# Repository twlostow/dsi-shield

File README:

DSI Core Readme
------------------------

0. Disclaimer

This project implements a MIPI DSI (MIPI Display Serial Interface) Verilog core.
Since the DSI specification is non-public and requires an NDA, the core was built
using bits and pieces available throughout the Web: presentations, display controller/SOC
datasheets, various application notes and Android kernel drivers. The author is not 
associated in any way with the MIPI Alliance. The core is provided as-is, it has never been
verified for compliance with the DSI standard and it probably lacks many of its features.
You use it at your own risk, there's no warranty.

1. License

- All HDL (unless otherwise noted) is released under LGPL v3.0
- All software (unless otherwise noted), is GPL v 3.0 or later.
- PCB design and schematics are licensed under CERN Open Hardware License v 1.2.

2. Acknowledgements

- Special thanks go to Sebastien Bourdeauducq, the creator of the Milkymist project, for his 
  excellent IP cores (HPDMC, FML and LM32 Xilinx port) used by in the DSI shield firmware.

- Andrew "Bunnie" Huang, for his EDID generation tools (Chumby WebTV project).

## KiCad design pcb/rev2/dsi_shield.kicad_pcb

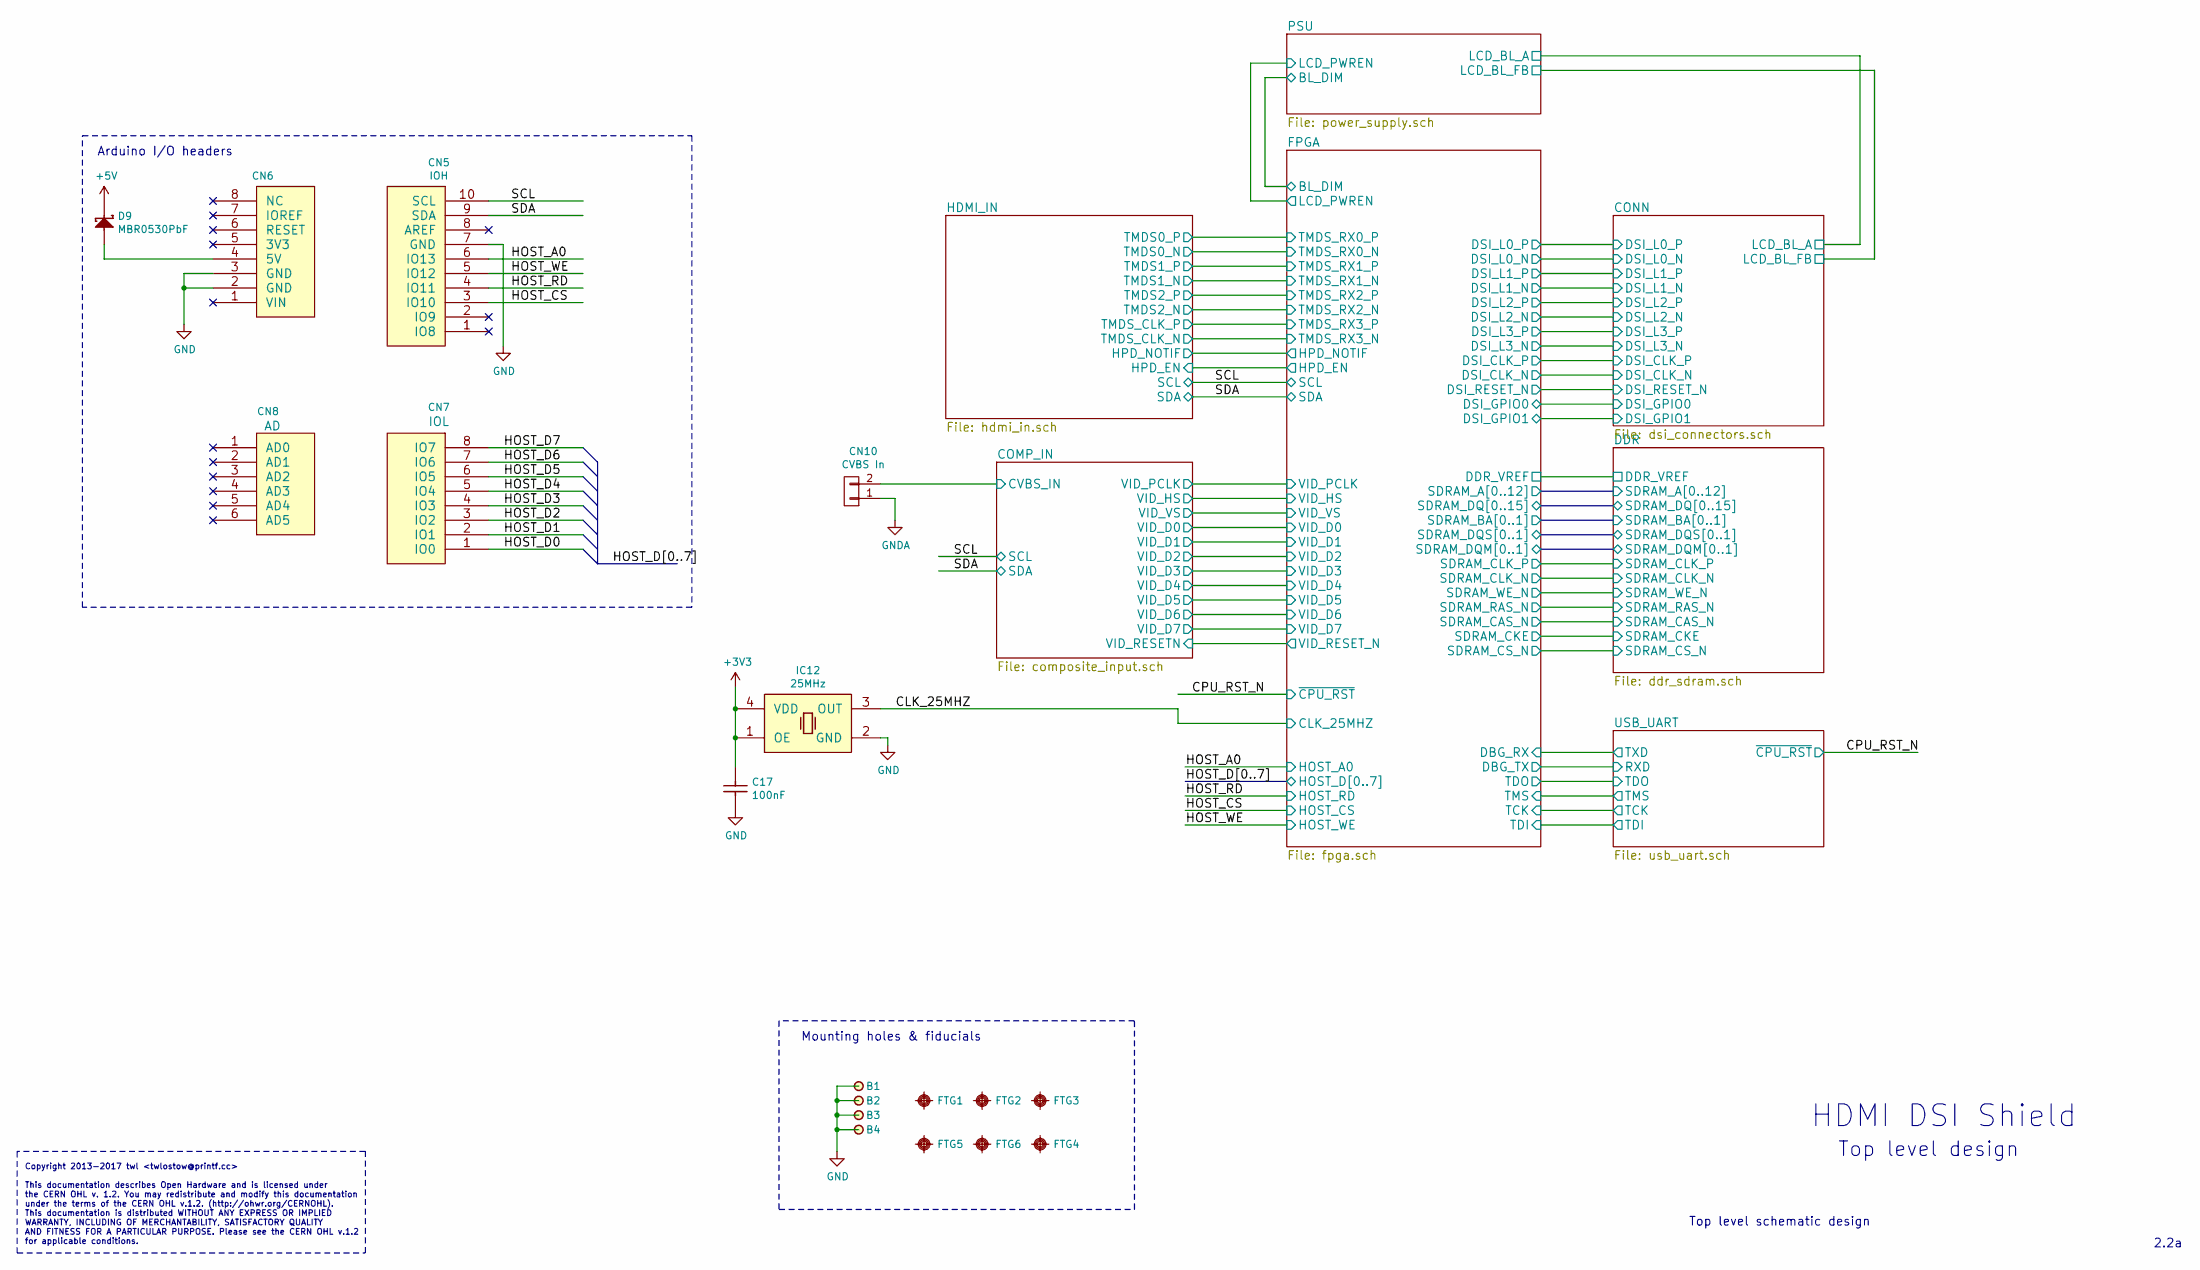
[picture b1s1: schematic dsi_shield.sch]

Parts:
B1, B2, B3, B4: PLATED_HOLE2.0_PAD3.5; c350h200; Part Number PLATED_HOLE2.0_PAD3.5
C17: CC0603_100NF_100V_10%_X7R; CAPC1608X90N; Voltage 100V; Tolerance ±10%; Part Number CC0603_100NF_100V_10%_X7R
CN5: IOH; Pin_Header_Straight_1x10
CN6: POWER_UNO; Pin_Header_Straight_1x08
CN7: IOL; Pin_Header_Straight_1x08
CN8: AD; Pin_Header_Straight_1x06
CN10: CVBS In; Pin_Header_Straight_1x02
D9: MBR0530PbF; SOD3715X145N; Voltage 30V; Part Number MBR0530PbF
FTG1, FTG2, FTG3, FTG4, FTG5, FTG6: FIDUCIAL_TARGET_S100-200; FIDUCIAL_TOP_S100-200; Part Number FIDUCIAL_TARGET_S100-200
IC12: OSC_25MHZ_PERICOM_FNETHE025; OSC_PERICOM_FNETHE025; Part Number OSC_25MHZ_PERICOM_FNETHE025

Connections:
+5V: D9.1 (C); also elsewhere on the board
/CLK_25MHZ: IC12.3 (OUT); also elsewhere on the board
/COMP_IN/CVBS_IN: CN10.2; also elsewhere on the board
/HOST_A0: CN5.6 (IO13); also elsewhere on the board
/HOST_CS: CN5.3 (IO10); also elsewhere on the board
/HOST_D0: CN7.1 (IO0); also elsewhere on the board
/HOST_D1: CN7.2 (IO1); also elsewhere on the board
/HOST_D2: CN7.3 (IO2); also elsewhere on the board
/HOST_D3: CN7.4 (IO3); also elsewhere on the board
/HOST_D4: CN7.5 (IO4); also elsewhere on the board
/HOST_D5: CN7.6 (IO5); also elsewhere on the board
/HOST_D6: CN7.7 (IO6); also elsewhere on the board
/HOST_D7: CN7.8 (IO7); also elsewhere on the board
/HOST_RD: CN5.4 (IO11); also elsewhere on the board
/HOST_WE: CN5.5 (IO12); also elsewhere on the board
/SCL: CN5.10 (SCL); also elsewhere on the board
/SDA: CN5.9 (SDA); also elsewhere on the board
GND: B1.1, B2.1, B3.1, B4.1, C17.2, CN5.7 (GND), CN6.2 (GND), CN6.3 (GND), IC12.2 (GND); also elsewhere on the board
GNDA: CN10.1; also elsewhere on the board
unnamed: CN6.4 (5V), D9.2 (A)

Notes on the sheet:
Copyright 2013-2017 twl <twlostow@printf.cc> This documentation describes Open Hardware and is licensed under the CERN OHL v. 1.2. You may redistribute and modify this documentation under the terms of the CERN OHL v.1.2. (http://ohwr.org/CERNOHL). This documentation is distributed WITHOUT ANY EXPRE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
HDMI DSI Shield
Top level design
2.2a
Top level schematic design
Mounting holes & fiducials
Arduino I/O headers

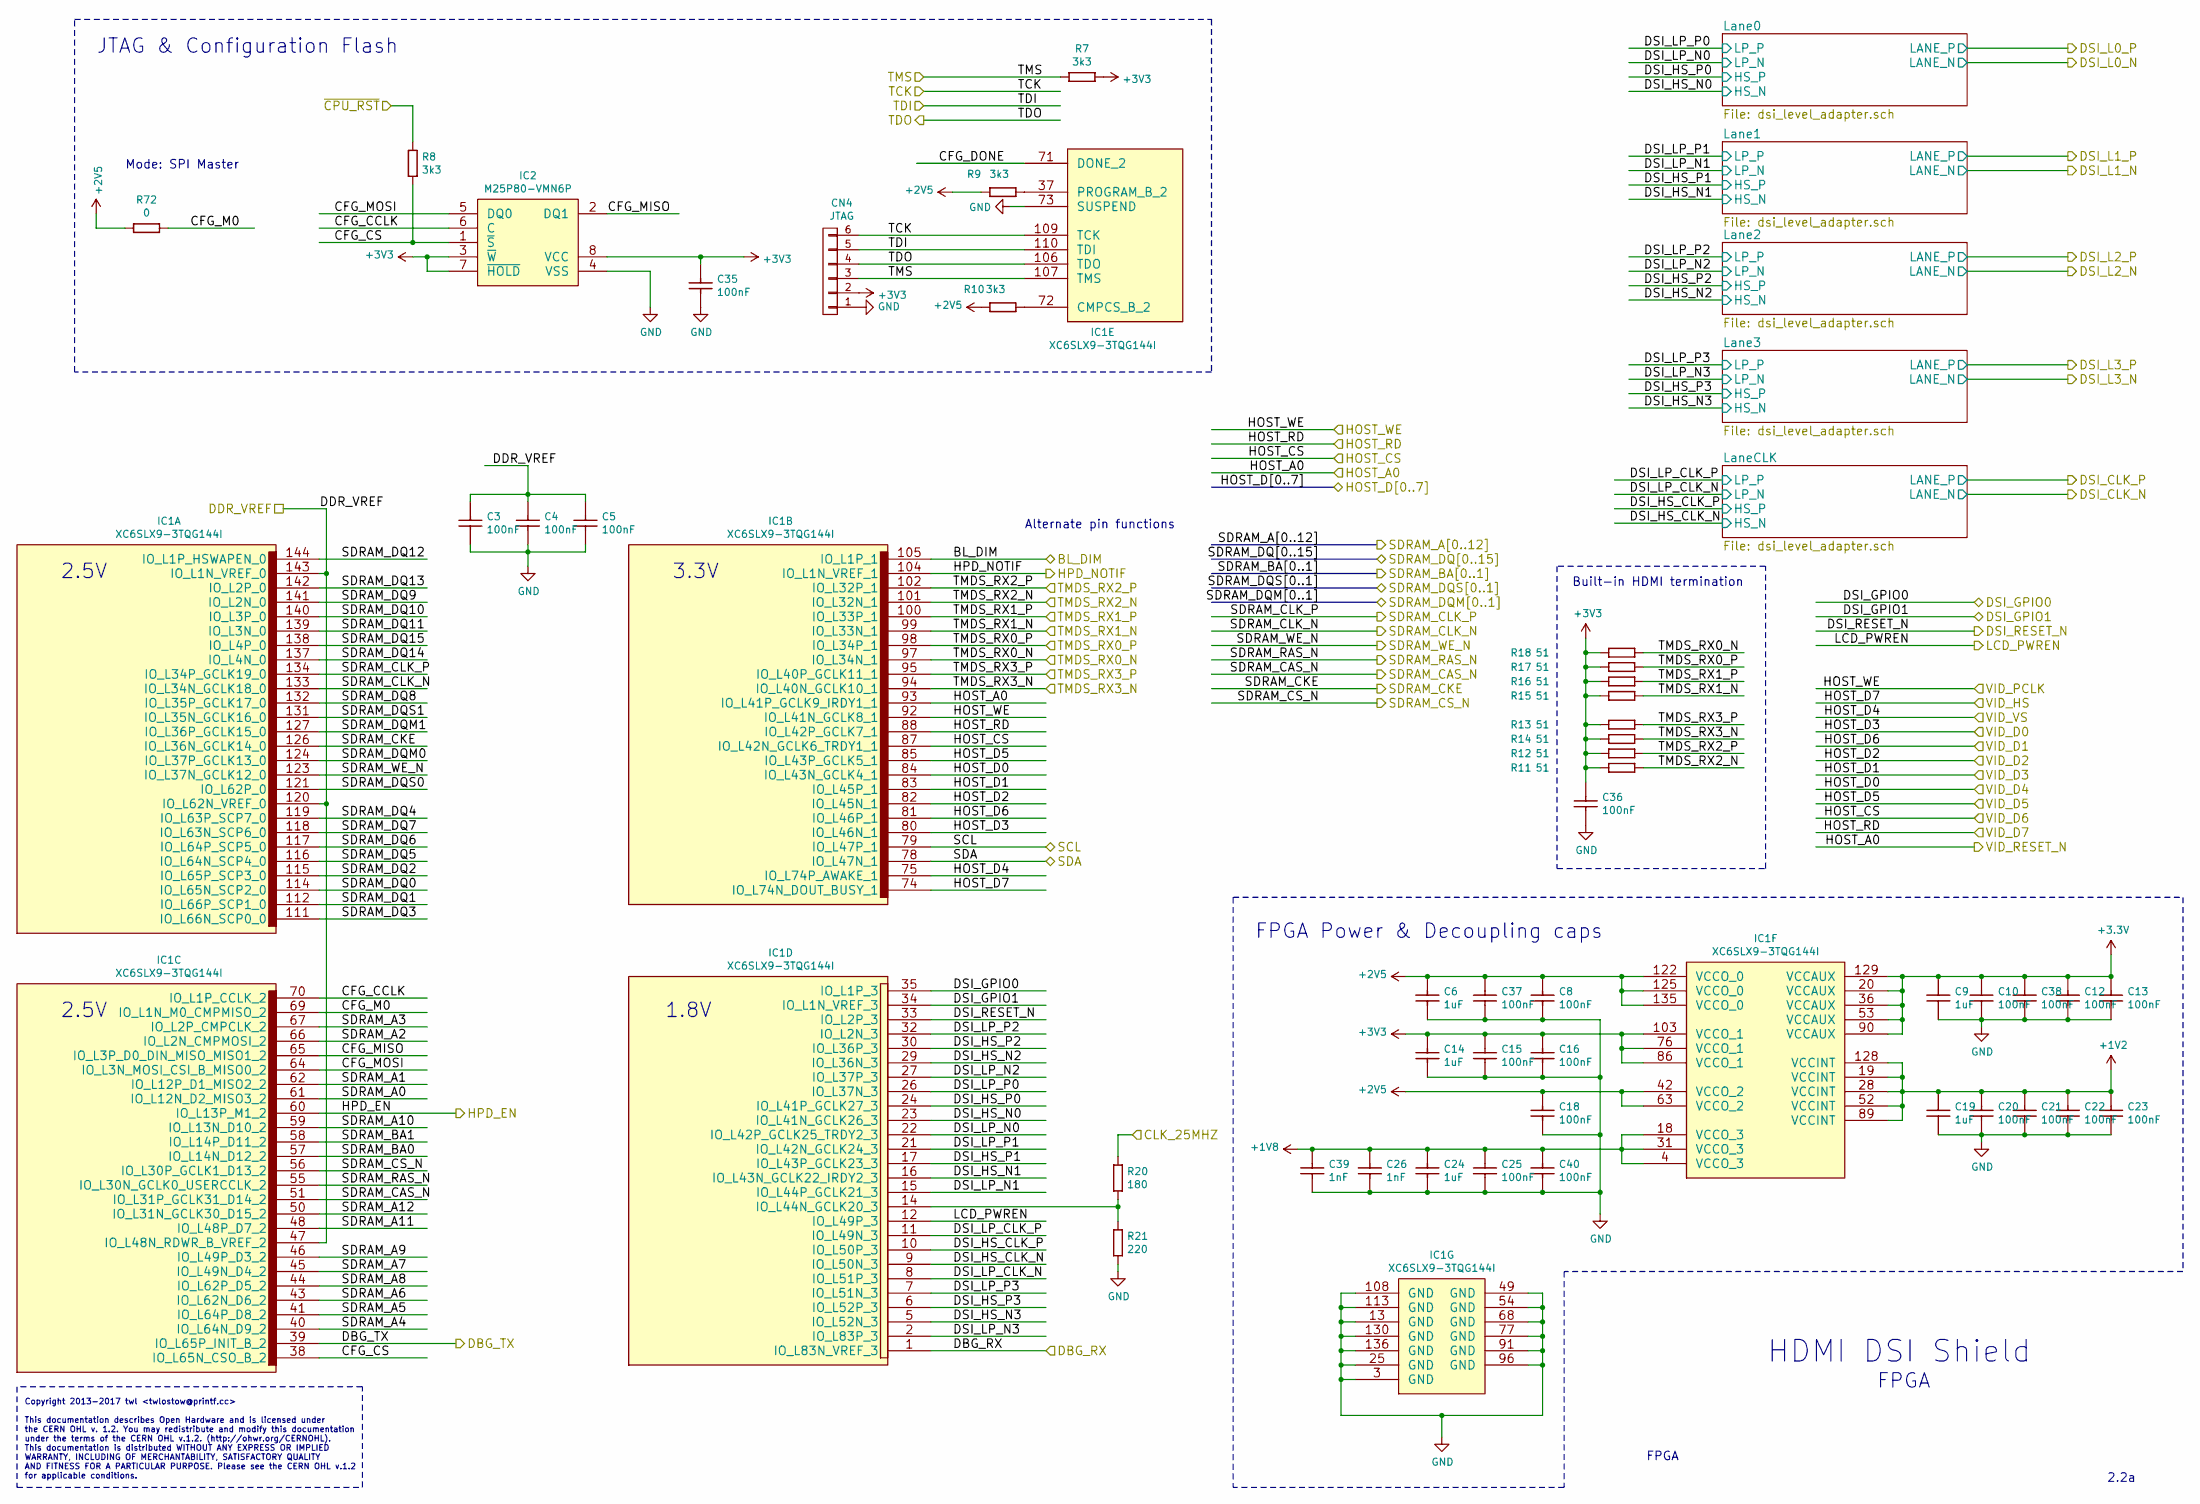
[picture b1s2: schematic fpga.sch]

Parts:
C3, C4, C5, C8, C10, C12, C13, C15, C16, C18, C20, C21, C22, C23, C25, C35, C36, C37, C38, C40: CC0603_100NF_50V_10%_X7R; CAPC1608X87N; Voltage 50V; Tolerance ±10%; Part Number CC0603_100NF_50V_10%_X7R
C6, C9, C14, C19, C24: CC0603_1UF_50V_10%_X5R; CAPC1608X87N; Voltage 50V; Tolerance ±10%; Part Number CC0603_1UF_50V_10%_X5R
C26, C39: CC0603_1NF_50V_5%_NP0; CAPC1608X90N; Voltage 50V; Tolerance ±5%; Part Number CC0603_1NF_50V_5%_NP0
CN4: JTAG; Pin_Header_Straight_1x06
IC1: XC6SLX9-3TQG144I; QFP50P2200X2200X160-144N; Part Number XC6SLX9-3TQG144I
IC2: M25P80-VMN6P; SOIC127P600X175-8N; Part Number M25P80-VMN6P
R7, R8, R9, R10: R0603_3K3_1%_0.1W_100PPM; RESC1608X55N; Voltage ~~; Tolerance ±1%; Part Number R0603_3K3_1%_0.1W_100PPM
R11, R12, R13, R14, R15, R16, R17, R18: R0603_51R_1%_0.1W_100PPM; RESC1608X55N; Voltage ~~; Tolerance ±1%; Part Number R0603_51R_1%_0.1W_100PPM
R20: R0603_180R_1%_0.1W_100PPM; RESC1608X55N; Voltage ~~; Tolerance ±1%; Part Number R0603_180R_1%_0.1W_100PPM
R21: R0603_220R_1%_0.1W_100PPM; RESC1608X55N; Voltage ~~; Tolerance ±1%; Part Number R0603_220R_1%_0.1W_100PPM
R72: R0603_0R_JUMPER; RESC1608X55N; Voltage ~~; Tolerance ~~; Part Number R0603_0R_JUMPER

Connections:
+1V2: C19.1, C20.1, C21.1, C22.1, C23.1, IC1.19 (VCCINT), IC1.28 (VCCINT), IC1.52 (VCCINT), IC1.89 (VCCINT), IC1.128 (VCCINT); also elsewhere on the board
+1V8: C24.1, C25.1, C26.1, C39.1, C40.1, IC1.4 (VCCO_3), IC1.18 (VCCO_3), IC1.31 (VCCO_3); also elsewhere on the board
+2V5: C6.1, C8.1, C18.1, C37.1, IC1.42 (VCCO_2), IC1.63 (VCCO_2), IC1.122 (VCCO_0), IC1.125 (VCCO_0), IC1.135 (VCCO_0), R9.2, R10.2, R72.1; also elsewhere on the board
/CLK_25MHZ: R20.1; also elsewhere on the board
/CONN/DSI_GPIO0: IC1.35 (IO_L1P_3); also elsewhere on the board
/CONN/DSI_GPIO1: IC1.34 (IO_L1N_VREF_3); also elsewhere on the board
/CONN/DSI_RESET_N: IC1.33 (IO_L2P_3); also elsewhere on the board
/CPU_RST_N: R8.2; also elsewhere on the board
/DDR/DDR_VREF: C3.1, C4.1, C5.1, IC1.47 (IO_L48N_RDWR_B_VREF_2), IC1.120 (IO_L62N_VREF_0), IC1.143 (IO_L1N_VREF_0); also elsewhere on the board
/DDR/SDRAM_A0: IC1.61 (IO_L12N_D2_MISO3_2); also elsewhere on the board
/DDR/SDRAM_A1: IC1.62 (IO_L12P_D1_MISO2_2); also elsewhere on the board
/DDR/SDRAM_A2: IC1.66 (IO_L2N_CMPMOSI_2); also elsewhere on the board
/DDR/SDRAM_A3: IC1.67 (IO_L2P_CMPCLK_2); also elsewhere on the board
/DDR/SDRAM_A4: IC1.40 (IO_L64N_D9_2); also elsewhere on the board
/DDR/SDRAM_A5: IC1.41 (IO_L64P_D8_2); also elsewhere on the board
/DDR/SDRAM_A6: IC1.43 (IO_L62N_D6_2); also elsewhere on the board
/DDR/SDRAM_A7: IC1.45 (IO_L49N_D4_2); also elsewhere on the board
/DDR/SDRAM_A8: IC1.44 (IO_L62P_D5_2); also elsewhere on the board
/DDR/SDRAM_A9: IC1.46 (IO_L49P_D3_2); also elsewhere on the board
/DDR/SDRAM_A10: IC1.59 (IO_L13N_D10_2); also elsewhere on the board
/DDR/SDRAM_A11: IC1.48 (IO_L48P_D7_2); also elsewhere on the board
/DDR/SDRAM_A12: IC1.50 (IO_L31N_GCLK30_D15_2); also elsewhere on the board
/DDR/SDRAM_BA0: IC1.57 (IO_L14N_D12_2); also elsewhere on the board
/DDR/SDRAM_BA1: IC1.58 (IO_L14P_D11_2); also elsewhere on the board
/DDR/SDRAM_CAS_N: IC1.51 (IO_L31P_GCLK31_D14_2); also elsewhere on the board
/DDR/SDRAM_CKE: IC1.126 (IO_L36N_GCLK14_0); also elsewhere on the board
/DDR/SDRAM_CLK_N: IC1.133 (IO_L34N_GCLK18_0); also elsewhere on the board
/DDR/SDRAM_CLK_P: IC1.134 (IO_L34P_GCLK19_0); also elsewhere on the board
/DDR/SDRAM_CS_N: IC1.56 (IO_L30P_GCLK1_D13_2); also elsewhere on the board
/DDR/SDRAM_DQ0: IC1.114 (IO_L65N_SCP2_0); also elsewhere on the board
/DDR/SDRAM_DQ1: IC1.112 (IO_L66P_SCP1_0); also elsewhere on the board
/DDR/SDRAM_DQ2: IC1.115 (IO_L65P_SCP3_0); also elsewhere on the board
/DDR/SDRAM_DQ3: IC1.111 (IO_L66N_SCP0_0); also elsewhere on the board
/DDR/SDRAM_DQ4: IC1.119 (IO_L63P_SCP7_0); also elsewhere on the board
/DDR/SDRAM_DQ5: IC1.116 (IO_L64N_SCP4_0); also elsewhere on the board
/DDR/SDRAM_DQ6: IC1.117 (IO_L64P_SCP5_0); also elsewhere on the board
/DDR/SDRAM_DQ7: IC1.118 (IO_L63N_SCP6_0); also elsewhere on the board
/DDR/SDRAM_DQ8: IC1.132 (IO_L35P_GCLK17_0); also elsewhere on the board
/DDR/SDRAM_DQ9: IC1.141 (IO_L2N_0); also elsewhere on the board
/DDR/SDRAM_DQ10: IC1.140 (IO_L3P_0); also elsewhere on the board
/DDR/SDRAM_DQ11: IC1.139 (IO_L3N_0); also elsewhere on the board
/DDR/SDRAM_DQ12: IC1.144 (IO_L1P_HSWAPEN_0); also elsewhere on the board
/DDR/SDRAM_DQ13: IC1.142 (IO_L2P_0); also elsewhere on the board
/DDR/SDRAM_DQ14: IC1.137 (IO_L4N_0); also elsewhere on the board
/DDR/SDRAM_DQ15: IC1.138 (IO_L4P_0); also elsewhere on the board
/DDR/SDRAM_DQM0: IC1.124 (IO_L37P_GCLK13_0); also elsewhere on the board
/DDR/SDRAM_DQM1: IC1.127 (IO_L36P_GCLK15_0); also elsewhere on the board
/DDR/SDRAM_DQS0: IC1.121 (IO_L62P_0); also elsewhere on the board
/DDR/SDRAM_DQS1: IC1.131 (IO_L35N_GCLK16_0); also elsewhere on the board
/DDR/SDRAM_RAS_N: IC1.55 (IO_L30N_GCLK0_USERCCLK_2); also elsewhere on the board
/DDR/SDRAM_WE_N: IC1.123 (IO_L37N_GCLK12_0); also elsewhere on the board
/FPGA/BL_DIM: IC1.105 (IO_L1P_1); also elsewhere on the board
/FPGA/CFG_CCLK: IC1.70 (IO_L1P_CCLK_2), IC2.6 (C)
/FPGA/CFG_CS: IC1.38 (IO_L65N_CSO_B_2), IC2.1 (~S), R8.1
/FPGA/CFG_DONE: IC1.71 (DONE_2)
/FPGA/CFG_M0: IC1.69 (IO_L1N_M0_CMPMISO_2), R72.2
/FPGA/CFG_MISO: IC1.65 (IO_L3P_D0_DIN_MISO_MISO1_2), IC2.2 (DQ1)
/FPGA/CFG_MOSI: IC1.64 (IO_L3N_MOSI_CSI_B_MISO0_2), IC2.5 (DQ0)
/FPGA/DBG_RX: IC1.1 (IO_L83N_VREF_3); also elsewhere on the board
/FPGA/DBG_TX: IC1.39 (IO_L65P_INIT_B_2); also elsewhere on the board
/FPGA/DSI_HS_CLK_N: IC1.9 (IO_L50N_3); also elsewhere on the board
/FPGA/DSI_HS_CLK_P: IC1.10 (IO_L50P_3); also elsewhere on the board
/FPGA/DSI_HS_N0: IC1.23 (IO_L41N_GCLK26_3); also elsewhere on the board
/FPGA/DSI_HS_N1: IC1.16 (IO_L43N_GCLK22_IRDY2_3); also elsewhere on the board
/FPGA/DSI_HS_N2: IC1.29 (IO_L36N_3); also elsewhere on the board
/FPGA/DSI_HS_N3: IC1.5 (IO_L52N_3); also elsewhere on the board
/FPGA/DSI_HS_P0: IC1.24 (IO_L41P_GCLK27_3); also elsewhere on the board
/FPGA/DSI_HS_P1: IC1.17 (IO_L43P_GCLK23_3); also elsewhere on the board
/FPGA/DSI_HS_P2: IC1.30 (IO_L36P_3); also elsewhere on the board
/FPGA/DSI_HS_P3: IC1.6 (IO_L52P_3); also elsewhere on the board
/FPGA/DSI_LP_CLK_N: IC1.8 (IO_L51P_3); also elsewhere on the board
/FPGA/DSI_LP_CLK_P: IC1.11 (IO_L49N_3); also elsewhere on the board
/FPGA/DSI_LP_N0: IC1.22 (IO_L42P_GCLK25_TRDY2_3); also elsewhere on the board
/FPGA/DSI_LP_N1: IC1.15 (IO_L44P_GCLK21_3); also elsewhere on the board
/FPGA/DSI_LP_N2: IC1.27 (IO_L37P_3); also elsewhere on the board
/FPGA/DSI_LP_N3: IC1.2 (IO_L83P_3); also elsewhere on the board
/FPGA/DSI_LP_P0: IC1.26 (IO_L37N_3); also elsewhere on the board
/FPGA/DSI_LP_P1: IC1.21 (IO_L42N_GCLK24_3); also elsewhere on the board
/FPGA/DSI_LP_P2: IC1.32 (IO_L2N_3); also elsewhere on the board
/FPGA/DSI_LP_P3: IC1.7 (IO_L51N_3); also elsewhere on the board
/FPGA/HPD_EN: IC1.60 (IO_L13P_M1_2); also elsewhere on the board
/FPGA/HPD_NOTIF: IC1.104 (IO_L1N_VREF_1); also elsewhere on the board
/FPGA/LCD_PWREN: IC1.12 (IO_L49P_3); also elsewhere on the board
/FPGA/TCK: CN4.6, IC1.109 (TCK); also elsewhere on the board
/FPGA/TDI: CN4.5, IC1.110 (TDI); also elsewhere on the board
/FPGA/TDO: CN4.4, IC1.106 (TDO); also elsewhere on the board
/FPGA/TMS: CN4.3, IC1.107 (TMS), R7.2; also elsewhere on the board
/HDMI_IN/TMDS0_N: IC1.97 (IO_L34N_1), R18.2; also elsewhere on the board
/HDMI_IN/TMDS0_P: IC1.98 (IO_L34P_1), R17.2; also elsewhere on the board
/HDMI_IN/TMDS1_N: IC1.99 (IO_L33N_1), R15.2; also elsewhere on the board
/HDMI_IN/TMDS1_P: IC1.100 (IO_L33P_1), R16.2; also elsewhere on the board
/HDMI_IN/TMDS2_N: IC1.101 (IO_L32N_1), R11.2; also elsewhere on the board
/HDMI_IN/TMDS2_P: IC1.102 (IO_L32P_1), R12.2; also elsewhere on the board
/HDMI_IN/TMDS_CLK_N: IC1.94 (IO_L40N_GCLK10_1), R14.2; also elsewhere on the board
/HDMI_IN/TMDS_CLK_P: IC1.95 (IO_L40P_GCLK11_1), R13.2; also elsewhere on the board
/HOST_A0: IC1.93 (IO_L41P_GCLK9_IRDY1_1); also elsewhere on the board
/HOST_CS: IC1.87 (IO_L42N_GCLK6_TRDY1_1); also elsewhere on the board
/HOST_D0: IC1.84 (IO_L43N_GCLK4_1); also elsewhere on the board
/HOST_D1: IC1.83 (IO_L45P_1); also elsewhere on the board
/HOST_D2: IC1.82 (IO_L45N_1); also elsewhere on the board
/HOST_D3: IC1.80 (IO_L46N_1); also elsewhere on the board
/HOST_D4: IC1.75 (IO_L74P_AWAKE_1); also elsewhere on the board
/HOST_D5: IC1.85 (IO_L43P_GCLK5_1); also elsewhere on the board
/HOST_D6: IC1.81 (IO_L46P_1); also elsewhere on the board
/HOST_D7: IC1.74 (IO_L74N_DOUT_BUSY_1); also elsewhere on the board
/HOST_RD: IC1.88 (IO_L42P_GCLK7_1); also elsewhere on the board
/HOST_WE: IC1.92 (IO_L41N_GCLK8_1); also elsewhere on the board
/SCL: IC1.79 (IO_L47P_1); also elsewhere on the board
/SDA: IC1.78 (IO_L47N_1); also elsewhere on the board
GND: C3.2, C4.2, C5.2, C6.2, C8.2, C9.2, C10.2, C12.2, C13.2, C14.2, C15.2, C16.2, C18.2, C19.2, C20.2, C21.2, C22.2, C23.2, C24.2, C25.2, C26.2, C35.2, C36.2, C37.2, C38.2, C39.2, C40.2, CN4.1, IC1.3 (GND), IC1.13 (GND), IC1.25 (GND), IC1.49 (GND), IC1.54 (GND), IC1.68 (GND), IC1.73 (SUSPEND), IC1.77 (GND), IC1.91 (GND), IC1.96 (GND), IC1.108 (GND), IC1.113 (GND), IC1.130 (GND), IC1.136 (GND), IC2.4 (VSS), R21.2; also elsewhere on the board
unnamed: IC1.14 (IO_L44N_GCLK20_3), R20.2, R21.1
unnamed: IC1.37 (PROGRAM_B_2), R9.1
unnamed: IC1.72 (CMPCS_B_2), R10.1

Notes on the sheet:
Mode: SPI Master
JTAG & Configuration Flash
2.5V
3.3V
1.8V
Built-in HDMI termination
FPGA Power & Decoupling caps
Copyright 2013-2017 twl <twlostow@printf.cc> This documentation describes Open Hardware and is licensed under the CERN OHL v. 1.2. You may redistribute and modify this documentation under the terms of the CERN OHL v.1.2. (http://ohwr.org/CERNOHL). This documentation is distributed WITHOUT ANY EXPRE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
Alternate pin functions
HDMI DSI Shield
FPGA
2.2a

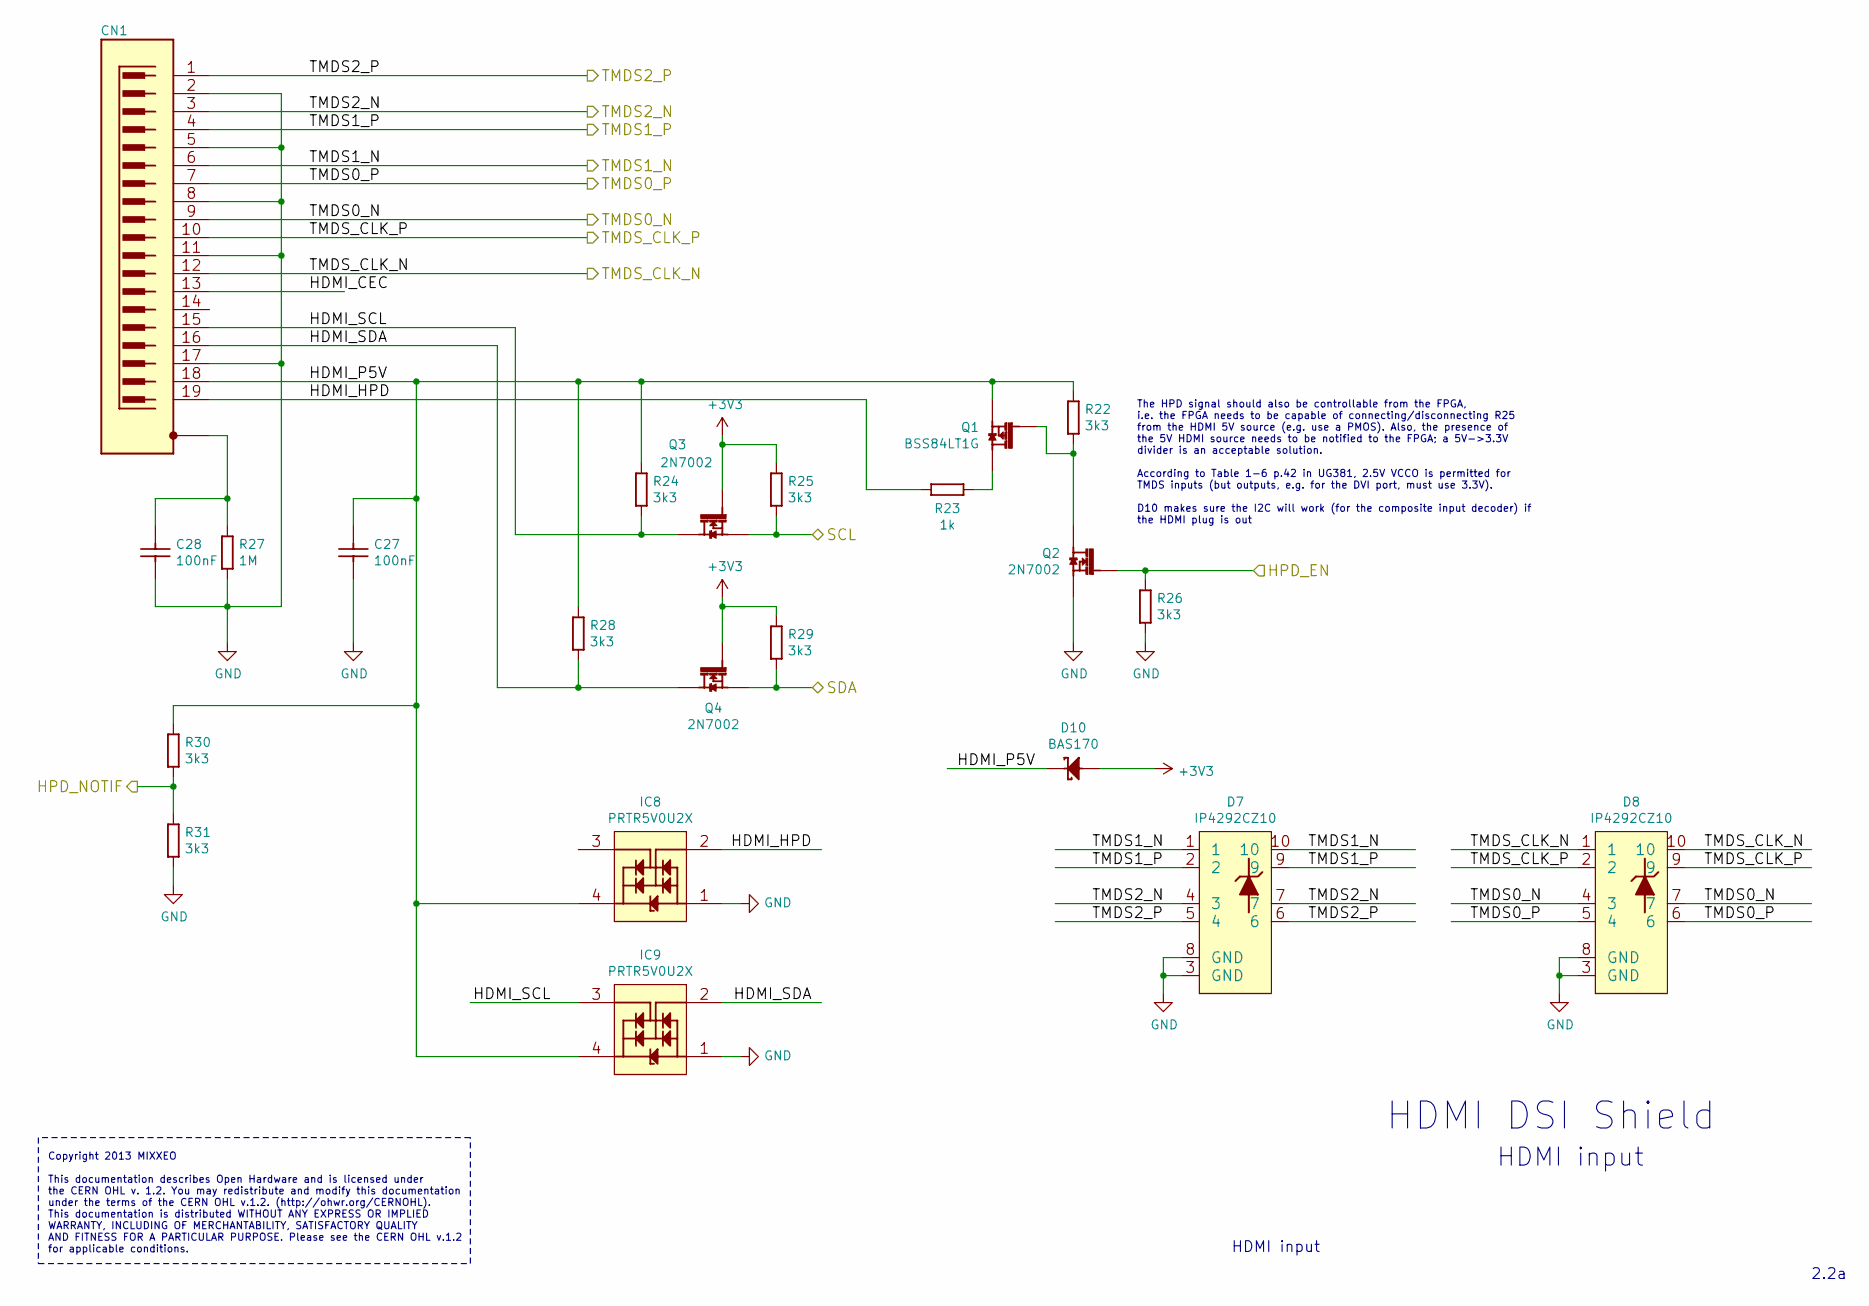
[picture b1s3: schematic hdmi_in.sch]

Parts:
C27, C28: CC0603_100NF_50V_10%_X7R; CAPC1608X87N; Voltage 50V; Tolerance ±10%; Part Number CC0603_100NF_50V_10%_X7R
CN1: MOLEX_500254-1927; Part Number MOLEX_500254-1927
D7, D8: IP4292CZ10; SOT1176-1
D10: BAS170; SOD2713X115N
IC8, IC9: PRTR5V0U2X; SOT190P230X110-4N; Voltage 5.5V; Part Number PRTR5V0U2X
Q1: BSS84LT1G; SOT95P240X110-3N; Part Number BSS84LT1G
Q2, Q3, Q4: 2N7002; SOT95P240X130-3N; Part Number 2N7002
R22, R24, R25, R26, R28, R29, R30, R31: R0603_3K3_1%_0.1W_100PPM; RESC1608X55N; Voltage ~~; Tolerance ±1%; Part Number R0603_3K3_1%_0.1W_100PPM
R23: R0603_1K_1%_0.1W_100PPM; RESC1608X55N; Voltage ~~; Tolerance ±1%; Part Number R0603_1K_1%_0.1W_100PPM
R27: R0603_1M_1%_0.1W_100PPM; RESC1608X55N; Voltage ~~; Tolerance ±1%; Part Number R0603_1M_1%_0.1W_100PPM

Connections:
/FPGA/HPD_EN: Q2.1 (G), R26.1; also elsewhere on the board
/FPGA/HPD_NOTIF: R30.2, R31.1; also elsewhere on the board
/HDMI_IN/HDMI_CEC: CN1.13
/HDMI_IN/HDMI_HPD: CN1.19, IC8.2 (I/O1), R23.1
/HDMI_IN/HDMI_P5V: C27.1, CN1.18, D10.1 (C), IC8.4 (VCC), IC9.4 (VCC), Q1.2 (S), R22.1, R24.1, R28.1, R30.1
/HDMI_IN/HDMI_SCL: CN1.15, IC9.3 (I/O2), Q3.3 (D), R24.2
/HDMI_IN/HDMI_SDA: CN1.16, IC9.2 (I/O1), Q4.3 (D), R28.2
/HDMI_IN/TMDS0_N: CN1.9, D8.4 (3), D8.7; also elsewhere on the board
/HDMI_IN/TMDS0_P: CN1.7, D8.5 (4), D8.6; also elsewhere on the board
/HDMI_IN/TMDS1_N: CN1.6, D7.1, D7.10; also elsewhere on the board
/HDMI_IN/TMDS1_P: CN1.4, D7.2, D7.9; also elsewhere on the board
/HDMI_IN/TMDS2_N: CN1.3, D7.4 (3), D7.7; also elsewhere on the board
/HDMI_IN/TMDS2_P: CN1.1, D7.5 (4), D7.6; also elsewhere on the board
/HDMI_IN/TMDS_CLK_N: CN1.12, D8.1, D8.10; also elsewhere on the board
/HDMI_IN/TMDS_CLK_P: CN1.10, D8.2, D8.9; also elsewhere on the board
/SCL: Q3.2 (S), R25.2; also elsewhere on the board
/SDA: Q4.2 (S), R29.2; also elsewhere on the board
GND: C27.2, C28.2, CN1.2, CN1.5, CN1.8, CN1.11, CN1.17, D7.3 (GND), D7.8 (GND), D8.3 (GND), D8.8 (GND), IC8.1 (GND), IC9.1 (GND), Q2.2 (S), R26.2, R27.2, R31.2; also elsewhere on the board
unnamed: C28.1, CN1.SHIE (SHIELD), R27.1
unnamed: Q1.1 (G), Q2.3 (D), R22.2
unnamed: Q1.3 (D), R23.2

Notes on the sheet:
The HPD signal should also be controllable from the FPGA, i.e. the FPGA needs to be capable of connecting/disconnecting R25 from the HDMI 5V source (e.g. use a PMOS). Also, the presence of the 5V HDMI source needs to be notified to the FPGA; a 5V->3.3V divider is an acceptable solution. According t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
Copyright 2013 MIXXEO This documentation describes Open Hardware and is licensed under the CERN OHL v. 1.2. You may redistribute and modify this documentation under the terms of the CERN OHL v.1.2. (http://ohwr.org/CERNOHL). This documentation is distributed WITHOUT ANY EXPRESS OR IMPLIED WARRANTY,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
HDMI DSI Shield
HDMI input
2.2a

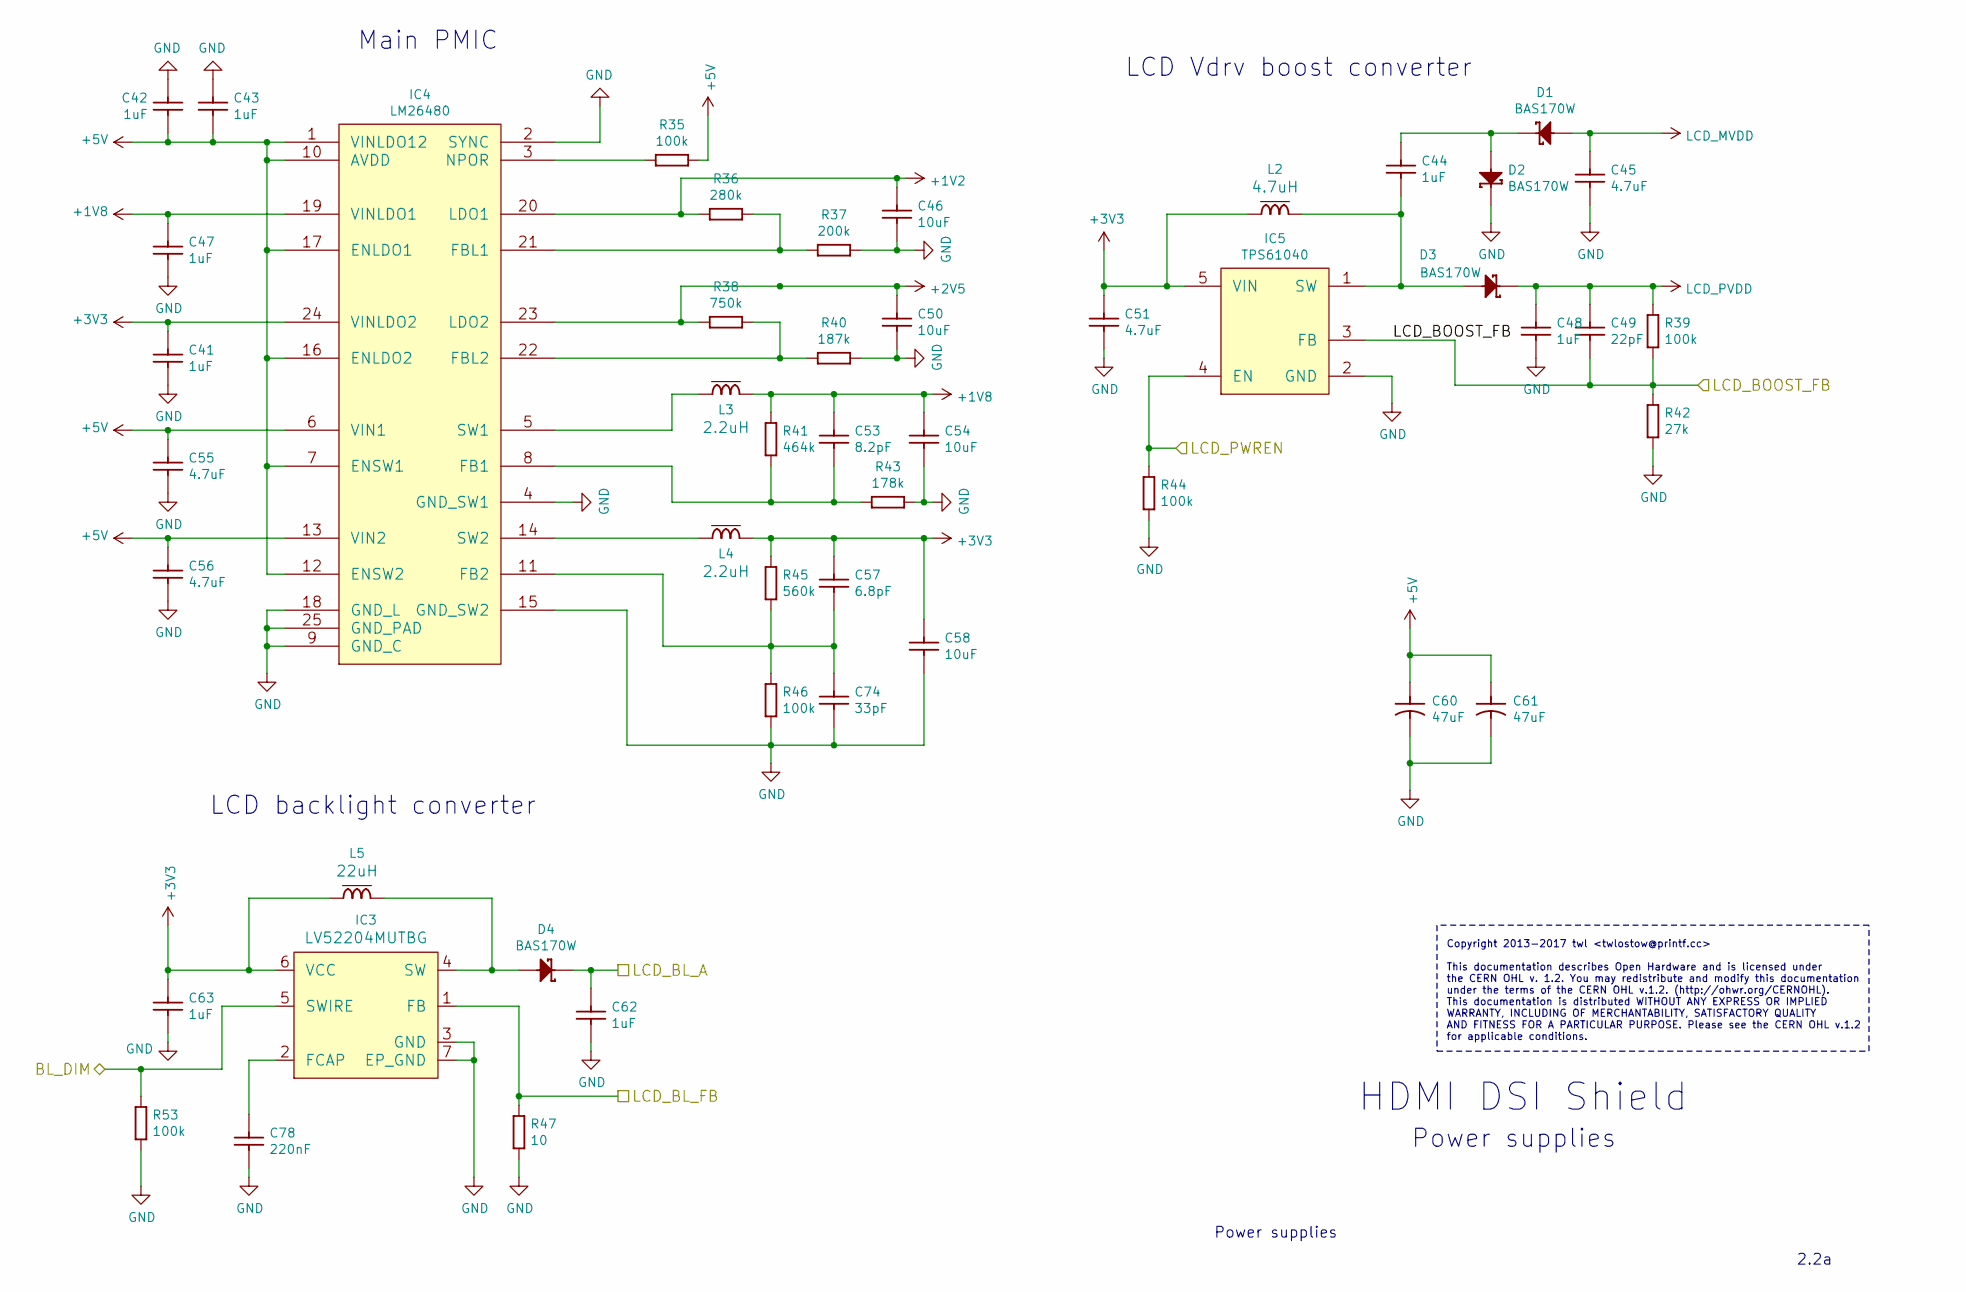
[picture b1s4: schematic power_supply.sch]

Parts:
C41, C42, C43, C44, C47, C48, C62, C63: CC0603_1UF_50V_10%_X5R; CAPC1608X87N; Voltage 50V; Tolerance ±10%; Part Number CC0603_1UF_50V_10%_X5R
C45, C51, C55, C56: CC0603_4.7UF_6.3V_10%_X5R; CAPC1608X87N; Voltage 6.3V; Tolerance ±10%; Part Number CC0603_4.7UF_6.3V_10%_X5R
C46, C50, C54, C58: CC0805_10UF_16V_10%_X5R; CAPC2012X135N; Voltage 16V; Tolerance ±10%; Part Number CC0805_10UF_16V_10%_X5R
C49: CC0603_22PF_50V_5%_NP0; CAPC1608X87N; Voltage 50V; Tolerance ±5%; Part Number CC0603_22PF_50V_5%_NP0
C53: CC0603_8.2PF_50V_0.5PF_NP0; CAPC1608X87N; Voltage 50V; Tolerance ±0.5pF; Part Number CC0603_8.2PF_50V_0.5PF_NP0
C57: CC0603_6.8PF_50V_0.5PF_NP0; CAPC1608X87N; Voltage 50V; Tolerance ±0.5pF; Part Number CC0603_6.8PF_50V_0.5PF_NP0
C60, C61: CTE3528-21_47UF_6.3V_10%_LESR0250; CAPMP3528X210N; Voltage 6.3V; Tolerance ±10%; Part Number CTE3528-21_47UF_6.3V_10%_LESR0250
C74: CC0603_33PF_50V_5%_NP0; CAPC1608X87N; Voltage 50V; Tolerance ±5%; Part Number CC0603_33PF_50V_5%_NP0
C78: CC0603_220NF_10V_10%_X7R; CAPC1608X87N; Voltage 10V; Tolerance ±10%; Part Number CC0603_220NF_10V_10%_X7R
D1, D2, D3, D4: BAS170W; SOD2713X115N
IC3: LV52204MUTBG; UDFN6_2X2_065P
IC4: LM26480; QFN50P400X400X80-25N-S230
IC5: TPS61040; SOT95P275X110-5N
L2: 4.7uH; IND_PANASONIC_ELLVEG; Manufacturer Part Number DLCSM0315D-4R7-K
L3, L4: 2.2uH; IND_PANASONIC_ELLVEG; Manufacturer Part Number DLCSM0315D-2R2-K
L5: 22uH; IND_PANASONIC_ELLVEG; Manufacturer Part Number DLCSM0315D-220M-K
R35, R39, R44, R46, R53: R0603_100K_1%_0.1W_100PPM; RESC1608X55N; Voltage ~~; Tolerance ±1%; Part Number R0603_100K_1%_0.1W_100PPM
R36: R0603_280K_1%_0.1W_100PPM; RESC1608X55N; Voltage ~~; Tolerance ±1%; Part Number R0603_270K_1%_0.1W_100PPM
R37: R0603_200K_1%_0.1W_100PPM; RESC1608X55N; Voltage ~~; Tolerance ±1%; Part Number R0603_200K_1%_0.1W_100PPM
R38: R0603_750K_1%_0.1W_100PPM; RESC1608X55N; Voltage ~~; Tolerance ±1%; Part Number R0603_750K_1%_0.1W_100PPM
R40: R0603_187K_1%_0.1W_100PPM; RESC1608X55N; Voltage ~~; Tolerance ±1%; Part Number R0603_187K_1%_0.1W_100PPM
R41: R0603_464K_1%_0.1W_100PPM; RESC1608X55N; Voltage ~~; Tolerance ±1%; Part Number R0603_464K_1%_0.1W_100PPM
R42: R0603_27K_1%_0.1W_100PPM; RESC1608X55N; Voltage ~~; Tolerance ±1%; Part Number R0603_27K_1%_0.1W_100PPM
R43: R0603_178K_1%_0.1W_100PPM; RESC1608X55N; Voltage ~~; Tolerance ±1%; Part Number R0603_178K_1%_0.1W_100PPM
R45: R0603_560K_1%_0.1W_100PPM; RESC1608X55N; Voltage ~~; Tolerance ±1%; Part Number R0603_560K_1%_0.1W_100PPM
R47: R0603_10R_1%_0.1W_200PPM; RESC1608X55N; Voltage ~~; Tolerance ±1%; Part Number R0603_10R_1%_0.1W_200PPM

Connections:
+1V2: C46.1, IC4.20 (LDO1), R36.1; also elsewhere on the board
+1V8: C47.1, C53.1, C54.1, IC4.19 (VINLDO1), L3.2, R41.1; also elsewhere on the board
+2V5: C50.1, IC4.23 (LDO2), R38.1; also elsewhere on the board
+5V: C42.2, C43.2, C55.1, C56.1, C60.1, C61.1, IC4.1 (VINLDO12), IC4.6 (VIN1), IC4.7 (ENSW1), IC4.10 (AVDD), IC4.12 (ENSW2), IC4.13 (VIN2), IC4.16 (ENLDO2), IC4.17 (ENLDO1), R35.2; also elsewhere on the board
/CONN/LCD_BL_A: C62.1, D4.1 (C); also elsewhere on the board
/CONN/LCD_BL_FB: IC3.1 (FB), R47.1; also elsewhere on the board
/FPGA/BL_DIM: IC3.5 (SWIRE), R53.1; also elsewhere on the board
/FPGA/LCD_PWREN: IC5.4 (EN), R44.1; also elsewhere on the board
/PSU/LCD_BOOST_FB: C49.2, IC5.3 (FB), R39.2, R42.1
GND: C41.2, C42.1, C43.1, C45.2, C46.2, C47.2, C48.2, C50.2, C51.2, C54.2, C55.2, C56.2, C58.2, C60.2, C61.2, C62.2, C63.2, C74.2, C78.2, D2.1 (C), IC3.3 (GND), IC3.7 (EP_GND), IC4.2 (SYNC), IC4.4 (GND_SW1), IC4.9 (GND_C), IC4.15 (GND_SW2), IC4.18 (GND_L), IC4.25 (GND_PAD), IC5.2 (GND), R37.2, R40.2, R42.2, R43.2, R44.2, R46.2, R47.2, R53.2; also elsewhere on the board
LCD_MVDD: C45.1, D1.2 (A); also elsewhere on the board
LCD_PVDD: C48.1, C49.1, D3.1 (C), R39.1; also elsewhere on the board
unnamed: C44.1, D1.1 (C), D2.2 (A)
unnamed: C44.2, D3.2 (A), IC5.1 (SW), L2.2
unnamed: C53.2, IC4.8 (FB1), R41.2, R43.1
unnamed: C57.2, C74.1, IC4.11 (FB2), R45.2, R46.1
unnamed: C78.1, IC3.2 (FCAP)
unnamed: D4.2 (A), IC3.4 (SW), L5.2
unnamed: IC4.3 (NPOR), R35.1
unnamed: IC4.5 (SW1), L3.1
unnamed: IC4.14 (SW2), L4.1
unnamed: IC4.21 (FBL1), R36.2, R37.1
unnamed: IC4.22 (FBL2), R38.2, R40.1

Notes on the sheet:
Main PMIC
LCD Vdrv boost converter
Copyright 2013-2017 twl <twlostow@printf.cc> This documentation describes Open Hardware and is licensed under the CERN OHL v. 1.2. You may redistribute and modify this documentation under the terms of the CERN OHL v.1.2. (http://ohwr.org/CERNOHL). This documentation is distributed WITHOUT ANY EXPRE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
HDMI DSI Shield
Power supplies
2.2a
LCD backlight converter

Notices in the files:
parts and their libraries:
This work is licensed under the Creative Commons CC-BY-SA 4.0 License. To the extent that circuit schematics that use Licensed Material can be considered to be ‘Adapted Material’, then the copyright holder waives article 3.b of the license with respect to these schematics.
